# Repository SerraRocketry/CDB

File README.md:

# Aviônica - Computador de Bordo

Este projeto é o computador de bordo (CDB) para o foguete SR1500 da equipe de foguetemodelismo Serra Rocketry. O CDB utiliza sensores e módulos para monitorar a altitude, localização GPS, e controlar a abertura do paraquedas para garantir um voo seguro.

## Funcionalidades

- Leitura de altitude utilizando o sensor BMP280.
- Monitoramento de localização GPS com o módulo GPS NEO-6m.
- Comunicação via LoRa para transmissão de dados com a base operacional.
- Controle de um servo motor para abertura do paraquedas.
- Armazenamento de dados em SPIFFS.
- Monitoramento de aceleração e giroscópio utilizando o sensor MPU6050.

## Hardware Utilizado

- ESP32
- Sensor de pressão BMP280
- Módulo GPS
- Módulo LoRa
- Servo motor
- Buzzer
- LED
- Step down
- Baterias Li-Po
- Sensor MPU6050

## Configuração de Pinos

- **BUZZER_PIN**: 15
- **SERVO_PIN**: 13
- **LED_PIN**: 2
- **RX_GPS**: 16
- **TX_GPS**: 17
- **SS_LORA**: 5
- **RST_LORA**: 14
- **DIO0_LORA**: 4

## Bibliotecas Utilizadas

- **Wire**
- **SPI**
- **Adafruit_BMP280**
- **ESP32Servo**
- **TinyGPS++**
- **FS**
- **SPIFFS**
- **LoRa**
- **dafruit_MPU6050**
- **Adafruit_Sensor**

## Estrutura do Código

- **setup()**: Configura os sensores, módulos e inicializa as variáveis.
- **loop()**: Realiza leituras periódicas dos sensores, verifica a altitude e controla a abertura do paraquedas.
- **setupSPIFFS()**: Inicializa o sistema de arquivos SPIFFS.
- **setupBMP()**: Configura o sensor BMP280.
- **setupLoRa()**: Inicializa o módulo LoRa.
- **setupMPU()**: Configura o sensor MPU6050.
- **setupServo()**: Configura o servo motor.
- **buzzSignal()**: Controla o buzzer e o LED para sinalização.
- **logData()**: Armazena os dados lidos em um arquivo.
- **handleParachute()**: Controla a abertura do paraquedas com base na altitude.
- **checkHighest()**: Verifica a maior altitude alcançada.
- **writeFile()**: Escreve dados no arquivo SPIFFS.
- **appendFile()**: Anexa dados ao arquivo SPIFFS.
- **printBoth()**: Imprime mensagens no serial e envia via LoRa.
- **sendLoRa()**: Envia mensagens via LoRa.
- **GPSData()**: Obtém dados do GPS (latitude, longitude, satélites, altitude, data e hora).
- **BMPData()**: Obtém dados do sensor BMP280 (altitude e pressão).
- **MPUData()**: Obtém dados do sensor MPU6050 (aceleração e giroscópio).
- **getDataString()**: Concatena os dados do GPS, BMP280 e MPU6050 em uma string.

## Códigos de Apoio

Os códigos contidos em `/Extras` são apoios ao desenvolvimento. Esses códigos são funcionais e testados.

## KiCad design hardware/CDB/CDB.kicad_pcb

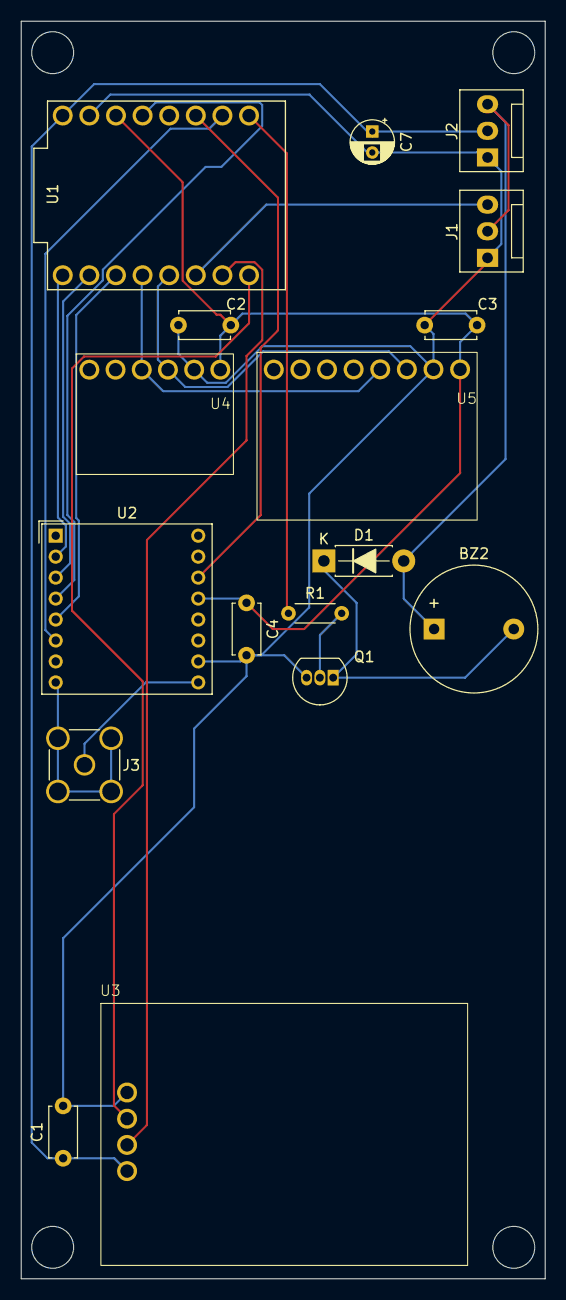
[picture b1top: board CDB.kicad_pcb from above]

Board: 2 copper layers, 50.0 x 120.0 mm, 17 parts (0 on the bottom side), 20 nets.

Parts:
BZ2: Buzzer; Buzzer_12x9.5RM7.6
C1, C2, C3, C4: 100nF; C_Disc_D4.7mm_W2.5mm_P5.00mm
C7: 10uF; CP_Radial_D4.0mm_P2.00mm
D1: 1N4007; D_DO-41_SOD81_P7.62mm_Horizontal
J1: Servo Motor; FanPinHeader_1x03_P2.54mm_Vertical
J2: Bateria; FanPinHeader_1x03_P2.54mm_Vertical
J3: Antena LoRa; SMA_Amphenol_901-144_Vertical
Q1: BC547; TO-92_Inline
R1: 1k; R_Axial_DIN0204_L3.6mm_D1.6mm_P5.08mm_Horizontal
U1: ESP32-C3; MODULE_ESP32-C3_SUPERMINI
U2: RFM95W; HOPERF_RFM9XW_THT
U3: GPS; GY-NEO6M-V2
U4: BMP280; GY-BMP280
U5: GY-521

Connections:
unnamed: BZ2.1 (+), D1.2 (A), J1.2, J2.3
unnamed: BZ2.2 (-), D1.1 (K), Q1.1 (C)
unnamed: C1.2, C2.2, C3.2, C4.2, C7.2, J1.1, J2.1, Q1.3 (E), U1.G (GND), U2.10 (GND), U3.1 (GND), U4.2 (GND), U5.2 (GND)
unnamed: J1.3, U1.10 (GPIO10)
unnamed: C1.1, C7.1, J2.2, U1.5V, U3.4 (VCC)
unnamed: J3.2 (Ext), U2.8 (GND)
unnamed: J3.1 (In), U2.9 (ANT)
unnamed: Q1.2 (B), R1.2
unnamed: C2.1, C3.1, C4.1, U1.3.3 (3V3), U2.13 (3.3V), U4.1 (VCC), U5.1 (VCC)
unnamed: R1.1, U1.0 (GPIO0)
unnamed: U1.1 (GPIO1), U2.6 (RESET)
unnamed: U1.2 (GPIO2), U2.14 (DIO0)
unnamed: U1.4 (GPIO4), U2.4 (SCK)
unnamed: U1.5 (GPIO5), U2.2 (MISO)
unnamed: U1.6 (GPIO6), U2.3 (MOSI)
unnamed: U1.7 (GPIO7), U2.5 (NSS)
unnamed: U1.8 (GPIO8), U4.4 (SDA), U5.4 (SDA)
unnamed: U1.9 (GPIO9), U4.3 (SCL), U5.3 (SCL)
unnamed: U1.20 (GPIO20), U3.3 (RX)
unnamed: U1.21 (GPIO21), U3.2 (TX)

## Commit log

2025-03-04 Upload
2025-03-04 Update setupSIM800
2025-03-04 Upadate readme
2025-03-04 Update geral
2025-04-15 RM SIM800L
2025-04-15 Update estrutura geral
2025-05-11 add mpu6050
2025-05-11 rename all
2025-05-15 add tests
2025-05-16 update little fs, File browser, open data, BOM
2025-05-30 update buzzer
2025-09-08 update na string de dados e no envio lora
2025-09-08 Feat: Adiciona arquivo inicial
    Esse sketch conterá código similar ao que está disponível no
    FileBrowser.ino, um servidor http para acesso facilitado aos sistema de
    arquivos internos do ESP32, contudo com o front-end e o back-end
    desacoplados.
2025-09-08 Feat: Adiciona Acess Point LAN ao ESP32
    Não adianta hospedar um servidor se não formos capazes de conectar a
    ele. A lib Wifi.h permite com que o ESP32 crie ou acesse uma rede LAN,
    nos dando assim tal acesso.
2025-09-08 Feat: Adiciona LittleFS como Sistema de Arquivos
    Antes de servirmos qualquer arquivo, devemos ser capazes de acessar tais
    arquivos. LittleFS irá ser o nosso Sistema de Arquivos que irá nos
    permitir ler, escrever, modificar e deletar arquivos no nosso sistema.
2025-09-08 Feat: Adiciona arquivos ao LittleFS
    Eventualmente precisaremos que os arquivos do site estejam disponíveis
    pelo LittleFS para que possamos hospedá-lo. Pra tornar esse processo de
    bootstrap menos trabalhoso tenho feito uso do plugin do ArduinoIDE
    arduino-littlefs-upload, que é acessível através do link
    https://github.com/earlephilhower/arduino-littlefs-upload/releases.
    Para que ocorra o upload é necessário que os arquivos estejam dentro da
2025-09-08 Feat: Adiciona servidor HTTP ao ESP32
    Além de inicializar o servidor também criei rotas básicas para os
    arquivos do site que enviei para o LittleFS.
2025-09-08 Feat: Popula a Home com arquivos do LittleFS
    Primeiramente criei uma rota nova que realiza uma consulta a todos os
    arquivos que estão disponíveis na raiz do LittleFS, os coloca em um JSON
    e o retorna como resposta. Tive que adicionar uma lib nova porque não
    sei fazer esse parsing na marra.
    Quanto ao front-end, adicionei um script que consome essa rota assim que
    o DOM carrega e popula uma tabela com os arquivos retornados. Essa
2025-09-08 Feat: Adiciona rota para arquivos individuais
    No backend adicionei uma rota que recebe um nome de arquivo específico,
    pesquisa por ele no LittleFS e o retorna caso encontrado.
    No frontend, modifiquei os links de abrir e baixar de cada arquivo da
    tabela para que apontem para essa mesma rota.
2025-09-09 Feat: Adiciona rota para deletar um arquivo
    Muito semelhante à rota anterior. No backend, só mudou praticamente o
    verbo HTTP no backend de GET para DELETE, e a ação correspondente
    (deletar o arquivo).
    Já no frontend, tive que atribuir um ouvinte de eventos ao botão
    correspondente com essa ação, já que apenas o verbo HTTP GET é
    implicitamente utilizado ao navegar a internet. Também removo a linha da
2025-09-12 Adição de um sketch com servidor http novo (#1)
    * Feat: Adiciona arquivo inicial
    Esse sketch conterá código similar ao que está disponível no
    FileBrowser.ino, um servidor http para acesso facilitado aos sistema de
    arquivos internos do ESP32, contudo com o front-end e o back-end
    desacoplados.
    * Feat: Adiciona Acess Point LAN ao ESP32
2025-10-01 add velocity threshold
2025-10-18 Feat: Remove arquivo de teste do FS
2025-10-18 Fix: Esconde arquivos da página web do cliente
    Nós usamos LittleFS para armazenar e recuperar logs do foguete, mas
    ele também é usado para armazenar os arquivos da página web que usamos
    para recuperar esses logs.
    Previamente, era possível ter acesso pela página web aos próprios
    arquivos da página web, incluindo a capacidade de acidentalmente
    deletá-los. Com esse commit, os arquivos da página foram movidos para
2025-10-18 Feat: Faz com que a pagina web atualize a cada 2s
    Uma pequena qualidade de vida. Não recarrega a página inteira, apenas
    pede pro servidor os arquivos mais recentes no LittleFS e reconstrói o
    DOM levando eles em consideração.
